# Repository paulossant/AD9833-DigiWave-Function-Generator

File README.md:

# AD9833-DigiWave-Function-Generator
DigiWave - Function Generator with STM32, analog amplification and touchscreen LCD

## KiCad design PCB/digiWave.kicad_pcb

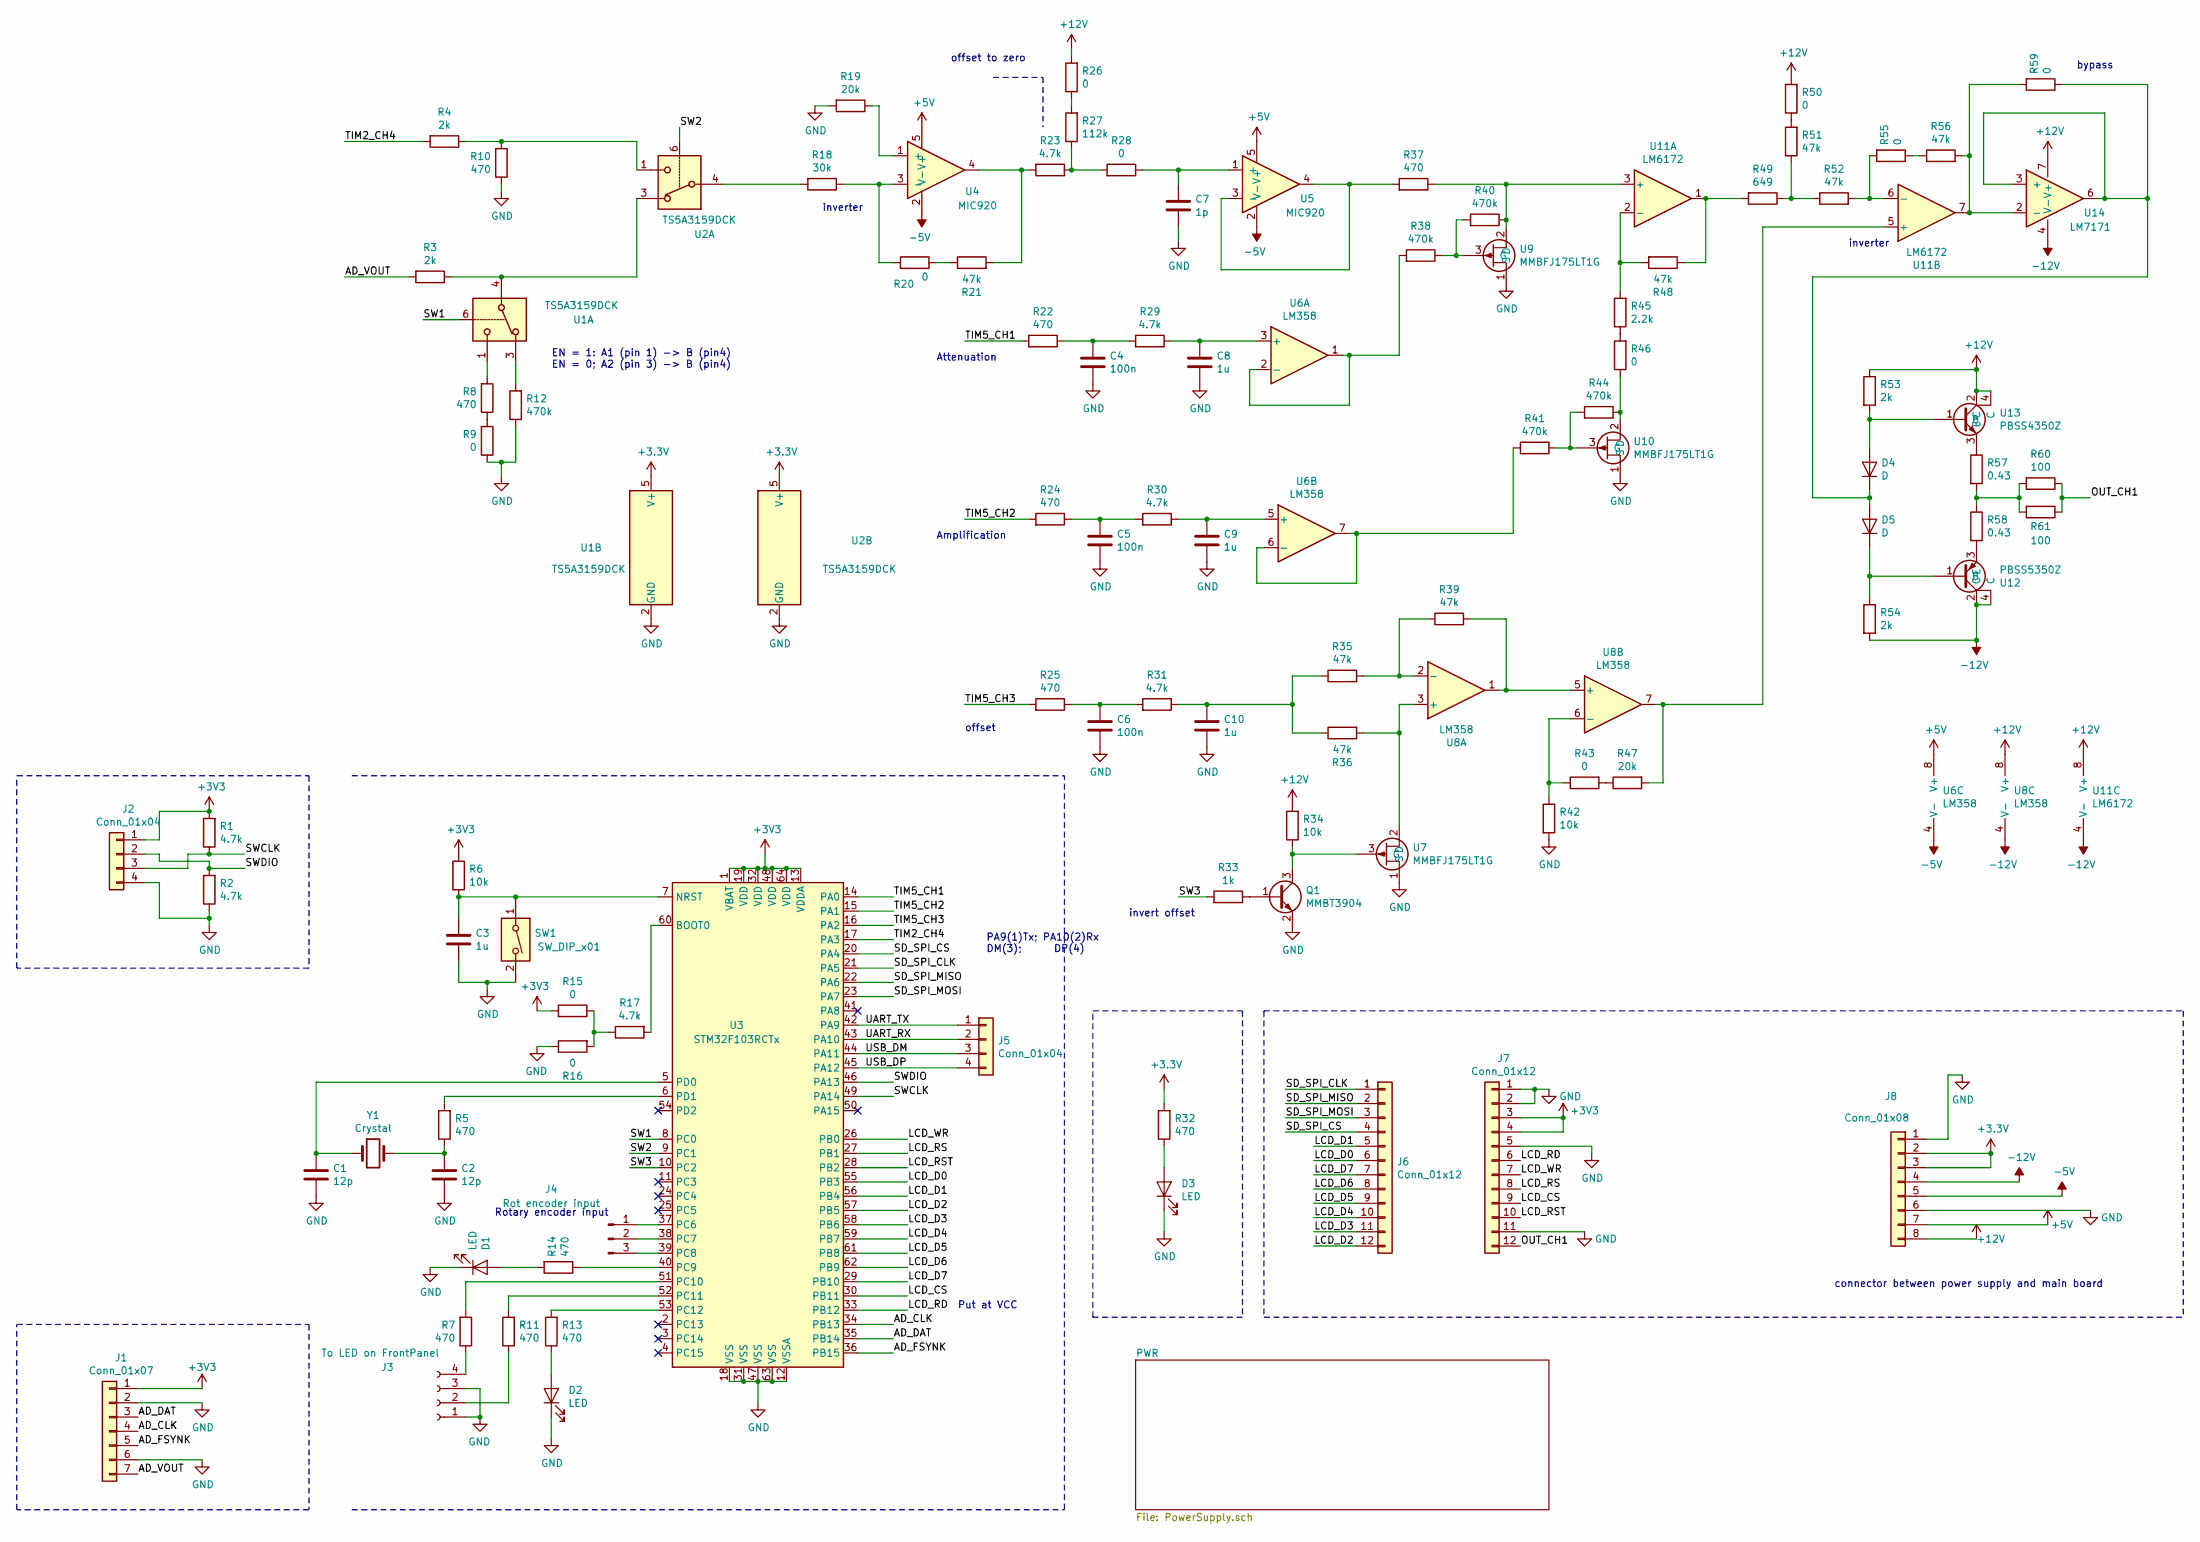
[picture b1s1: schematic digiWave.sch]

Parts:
C1, C2: 12p; C_0805_2012Metric_Pad1.15x1.40mm_HandSolder
C3, C8, C9, C10: 1u; C_0805_2012Metric_Pad1.15x1.40mm_HandSolder
C4, C5, C6: 100n; C_0805_2012Metric_Pad1.15x1.40mm_HandSolder
C7: 1p; C_0805_2012Metric_Pad1.15x1.40mm_HandSolder
D1, D2, D3: LED; LED_0805_2012Metric_Pad1.15x1.40mm_HandSolder
D4, D5: D; D_SOD-123
J1: Conn_01x07; PinHeader_1x07_P2.54mm_Vertical
J2, J5: Conn_01x04; PinHeader_1x04_P2.54mm_Vertical
J3: To LED on FrontPanel; PinSocket_1x04_P2.54mm_Vertical
J4: Rot encoder input; PinHeader_1x03_P2.54mm_Vertical
J6, J7: Conn_01x12; PinSocket_1x12_P2.54mm_Vertical
J8: Conn_01x08; PinHeader_1x08_P2.54mm_Vertical
Q1: MMBT3904; SOT-23_Handsoldering
R1, R2, R17, R23, R29, R30, R31: 4.7k; R_0805_2012Metric_Pad1.15x1.40mm_HandSolder
R3, R4, R53, R54: 2k; R_0805_2012Metric_Pad1.15x1.40mm_HandSolder
R5, R7, R8, R10, R11, R13, R14, R22, R24, R25, R32, R37: 470; R_0805_2012Metric_Pad1.15x1.40mm_HandSolder
R6, R34, R42: 10k; R_0805_2012Metric_Pad1.15x1.40mm_HandSolder
R9, R15, R16, R20, R26, R28, R43, R46, R50, R55, R59: 0; R_0805_2012Metric_Pad1.15x1.40mm_HandSolder
R12, R38, R40, R41, R44: 470k; R_0805_2012Metric_Pad1.15x1.40mm_HandSolder
R18: 30k; R_0805_2012Metric_Pad1.15x1.40mm_HandSolder
R19, R47: 20k; R_0805_2012Metric_Pad1.15x1.40mm_HandSolder
R21, R35, R36, R39, R48, R51, R52, R56: 47k; R_0805_2012Metric_Pad1.15x1.40mm_HandSolder
R27: 112k; R_0805_2012Metric_Pad1.15x1.40mm_HandSolder
R33: 1k; R_0805_2012Metric_Pad1.15x1.40mm_HandSolder
R45: 2.2k; R_0805_2012Metric_Pad1.15x1.40mm_HandSolder
R49: 649; R_0805_2012Metric_Pad1.15x1.40mm_HandSolder
R57, R58: 0.43; R_0805_2012Metric_Pad1.15x1.40mm_HandSolder
R60, R61: 100; R_1206_3216Metric_Pad1.42x1.75mm_HandSolder
SW1: SW_DIP_x01; SW_PUSH_6mm_H4.3mm
U1, U2: TS5A3159DCK; SOT-363_SC-70-6_Handsoldering
U3: STM32F103RCTx; QFP-64_10x10_Pitch0.5mm
U4, U5: MIC920; SOT-23-5_HandSoldering
U6, U8: LM358; SOIC-8_3.9x4.9mm_P1.27mm
U7, U9, U10: MMBFJ175LT1G; SOT-23_Handsoldering
U11: LM6172; SOIC-8_3.9x4.9mm_P1.27mm
U12: PBSS5350Z; SOT-223
U13: PBSS4350Z; SOT-223
U14: LM7171; SOIC-8_3.9x4.9mm_P1.27mm
Y1: Crystal; Crystal_HC49-4H_Vertical

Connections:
+5V: J8.7, U4.5 (V+), U5.5 (V+), U6.8 (V+)
+12V: J8.8, R26.2, R34.2, R50.2, R53.1, U8.8 (V+), U11.8 (V+), U13.2 (C), U13.4 (C), U14.7 (V+)
-5V: J8.5, U4.2 (V-), U5.2 (V-), U6.4 (V-)
-12V: J8.4, R54.2, U8.4 (V-), U11.4 (V-), U12.2 (C), U12.4 (C), U14.4 (V-)
/AD_CLK: J1.4, U3.34 (PB13)
/AD_DAT: J1.3, U3.35 (PB14)
/AD_FSYNK: J1.5, U3.36 (PB15)
/AD_VOUT: J1.7, R3.2
/LCD_CS: J7.9, U3.30 (PB11)
/LCD_D0: J6.6, U3.55 (PB3)
/LCD_D1: J6.5, U3.56 (PB4)
/LCD_D2: J6.12, U3.57 (PB5)
/LCD_D3: J6.11, U3.58 (PB6)
/LCD_D4: J6.10, U3.59 (PB7)
/LCD_D5: J6.9, U3.61 (PB8)
/LCD_D6: J6.8, U3.62 (PB9)
/LCD_D7: J6.7, U3.29 (PB10)
/LCD_RD: J7.6, U3.33 (PB12)
/LCD_RS: J7.8, U3.27 (PB1)
/LCD_RST: J7.10, U3.28 (PB2)
/LCD_WR: J7.7, U3.26 (PB0)
/OUT_CH1: J7.12, R60.1, R61.1
/SD_SPI_CLK: J6.1, U3.21 (PA5)
/SD_SPI_CS: J6.4, U3.20 (PA4)
/SD_SPI_MISO: J6.2, U3.22 (PA6)
/SD_SPI_MOSI: J6.3, U3.23 (PA7)
/SW1: U1.6, U3.8 (PC0)
/SW2: U2.6, U3.9 (PC1)
/SW3: R33.2, U3.10 (PC2)
/SWCLK: J2.3, R1.1, U3.49 (PA14)
/SWDIO: J2.2, R2.2, U3.46 (PA13)
/TIM2_CH4: R4.2, U3.17 (PA3)
/TIM5_CH1: R22.2, U3.14 (PA0)
/TIM5_CH2: R24.2, U3.15 (PA1)
/TIM5_CH3: R25.2, U3.16 (PA2)
/UART_RX: J5.2, U3.43 (PA10)
/UART_TX: J5.1, U3.42 (PA9)
/USB_DM: J5.3, U3.44 (PA11)
/USB_DP: J5.4, U3.45 (PA12)
GND: C1.2, C2.2, C3.1, C4.2, C5.2, C6.2, C7.2, C8.2, C9.2, C10.2, D1.1 (K), D2.1 (K), D3.1 (K), J1.2, J1.6, J2.4, J3.1, J3.3, J7.1, J7.2, J7.5, J7.11, J8.1, J8.6, Q1.2 (E), R2.1, R9.1, R10.1, R12.1, R16.1, R19.2, R42.2, SW1.2, U1.2 (GND), U2.2 (GND), U3.12 (VSSA), U3.18 (VSS), U3.31 (VSS), U3.47 (VSS), U3.63 (VSS), U7.1 (S), U9.1 (S), U10.1 (S); also elsewhere on the board
unnamed: C1.1, U3.5 (PD0), Y1.1
unnamed: C2.1, R5.1, Y1.2
unnamed 50: C3.2, R6.2, SW1.1, U3.7 (NRST); also elsewhere on the board
unnamed: C4.1, R22.1, R29.2
unnamed: C5.1, R24.1, R30.2
unnamed: C6.1, R25.1, R31.2
unnamed: C7.1, R28.1, U5.1 (+)
unnamed: C8.1, R29.1, U6.3 (+)
unnamed: C9.1, R30.1, U6.5 (+)
unnamed: C10.1, R31.1, R35.1, R36.1
unnamed: D1.2 (A), R14.2
unnamed: D2.2 (A), R13.1
unnamed: D3.2 (A), R32.1
unnamed: D4.1 (K), D5.2 (A), R59.1, U14.3 (+), U14.6
unnamed: D4.2 (A), R53.2, U13.1 (B)
unnamed: D5.1 (K), R54.1, U12.1 (B)
unnamed: J3.2, R11.1
unnamed: J3.4, R7.1
unnamed: J4.1, U3.37 (PC6)
unnamed: J4.2, U3.38 (PC7)
unnamed: J4.3, U3.39 (PC8)
unnamed: Q1.1 (B), R33.1
unnamed: Q1.3 (C), R34.1, U7.3 (G)
unnamed: R3.1, U1.4, U2.3
unnamed: R5.2, U3.6 (PD1)
unnamed: R7.2, U3.51 (PC10)
unnamed: R8.1, R9.2
unnamed: R8.2, U1.1
unnamed: R4.1, R10.2, U2.1
unnamed: R11.2, U3.52 (PC11)
unnamed: R12.2, U1.3
unnamed: R13.2, U3.53 (PC12)
unnamed: R14.1, U3.40 (PC9)
unnamed: R15.1, R16.2, R17.1
unnamed: R17.2, U3.60 (BOOT0)
unnamed: R18.1, R20.2, U4.3 (-)
unnamed: R18.2, U2.4
unnamed: R19.1, U4.1 (+)
unnamed: R20.1, R21.1
unnamed: R21.2, R23.2, U4.4
unnamed: R23.1, R27.1, R28.2
unnamed: R26.1, R27.2
unnamed: R35.2, R39.1, U8.2 (-)
unnamed: R36.2, U7.2 (D), U8.3 (+)
unnamed: R37.1, R40.1, U9.2 (D), U11.3 (+)
unnamed: R37.2, U5.3 (-), U5.4
unnamed: R38.1, R40.2, U9.3 (G)
unnamed: R38.2, U6.1, U6.2 (-)
unnamed: R39.2, U8.1, U8.5 (+)
unnamed: R41.1, R44.2, U10.3 (G)
unnamed: R41.2, U6.6 (-), U6.7
unnamed: R42.1, R43.1, U8.6 (-)
unnamed: R43.2, R47.1
unnamed: R44.1, R46.1, U10.2 (D)
unnamed: R45.1, R46.2
unnamed: R45.2, R48.2, U11.2 (-)
unnamed: R47.2, U8.7, U11.5 (+)
unnamed: R48.1, R49.2, U11.1
unnamed: R49.1, R51.1, R52.1
unnamed: R50.1, R51.2
unnamed: R52.2, R55.2, U11.6 (-)
unnamed: R55.1, R56.1
unnamed: R56.2, R59.2, U11.7, U14.2 (-)
unnamed: R57.1, U13.3 (E)
unnamed: R57.2, R58.1, R60.2, R61.2
unnamed: R58.2, U12.3 (E)

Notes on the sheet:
Put at VCC
offset to zero
bypass
EN = 1: A1 (pin 1) -> B (pin4) EN = 0; A2 (pin 3) -> B (pin4)
Attenuation
Amplification
invert offset
offset
inverter
connector between power supply and main board
PA9(1)Tx; PA10(2)Rx DM(3); DP(4)
Rotary encoder input

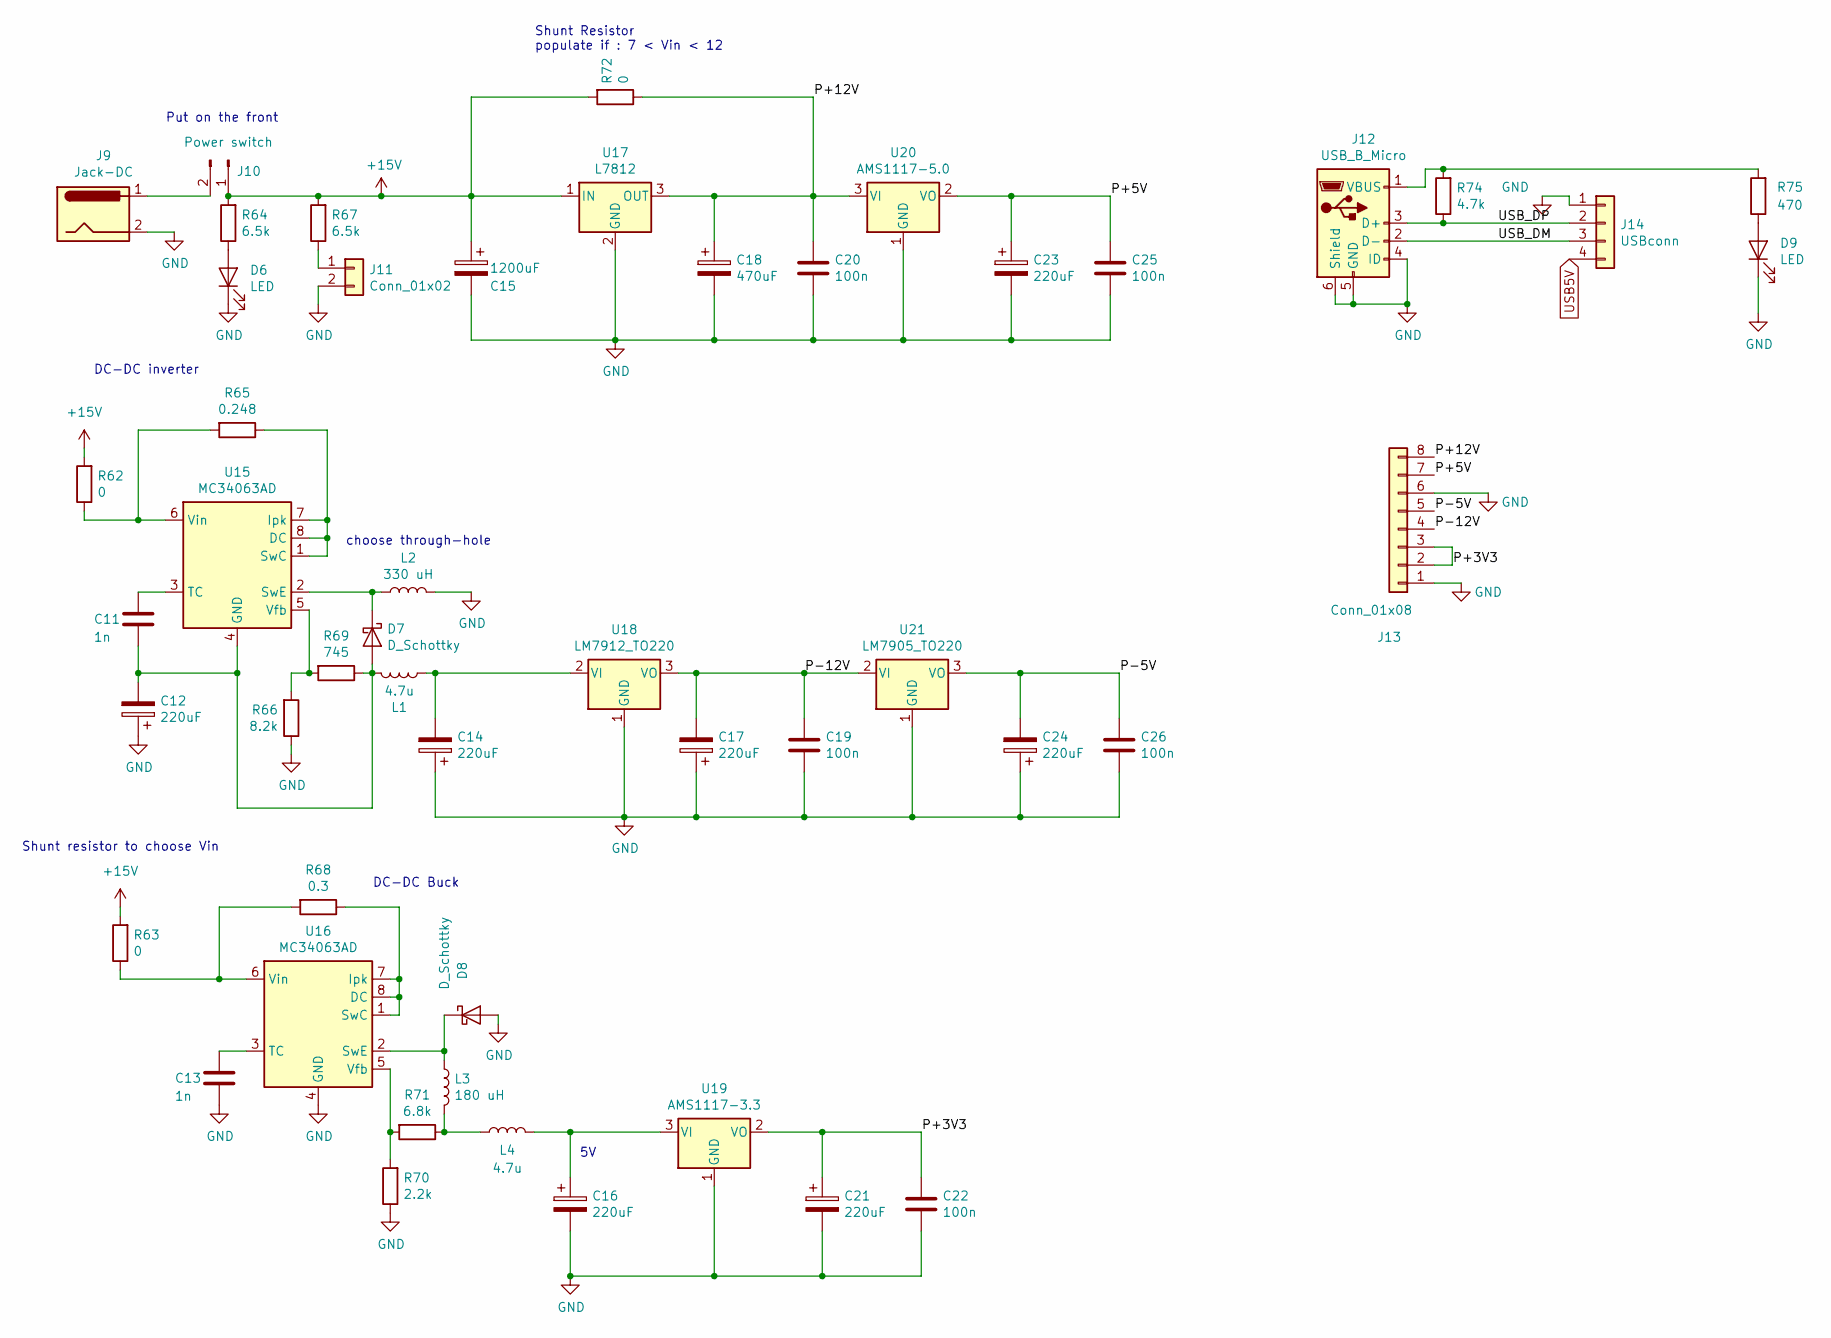
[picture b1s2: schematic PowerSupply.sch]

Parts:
C11, C13: 1n; C_Disc_D3.8mm_W2.6mm_P2.50mm
C12, C14, C16, C17, C21, C23, C24: 220uF; CP_Radial_D6.3mm_P2.50mm
C15: 1200uF; CP_Radial_D12.5mm_P5.00mm
C18: 470uF; CP_Radial_D8.0mm_P3.50mm
C19, C20, C22, C25, C26: 100n; C_0805_2012Metric_Pad1.15x1.40mm_HandSolder
D6, D9: LED; LED_0805_2012Metric_Pad1.15x1.40mm_HandSolder
D7, D8: D_Schottky; D_1812_4532Metric_Pad1.30x3.40mm_HSolder
J9: Jack-DC; Connector_BarrelJack
J10: Power switch; PinHeader_1x02_P2.54mm_Vertical
J11: Conn_01x02; PinHeader_1x02_P2.54mm_Vertical
J12: USB_B_Micro; USB_Micro-B_mine
J13: Conn_01x08; PinHeader_1x08_P2.54mm_Vertical
J14: USBconn; PinHeader_1x04_P2.54mm_Vertical
L1, L4: 4.7u; L_0805_2012Metric_Pad1.15x1.40mm_HandSolder
L2: 330 uH; L_Radial_D9.5mm_P5.00mm_Fastron_07HVP
L3: 180 uH; L_Radial_D9.5mm_P5.00mm_Fastron_07HVP
R62, R63, R72: 0; R_0805_2012Metric_Pad1.15x1.40mm_HandSolder
R64, R67: 6.5k; R_0805_2012Metric_Pad1.15x1.40mm_HandSolder
R65: 0.248; R_0805_2012Metric_Pad1.15x1.40mm_HandSolder
R66: 8.2k; R_0805_2012Metric_Pad1.15x1.40mm_HandSolder
R68: 0.3; R_0805_2012Metric_Pad1.15x1.40mm_HandSolder
R69: 745; R_0805_2012Metric_Pad1.15x1.40mm_HandSolder
R70: 2.2k; R_0805_2012Metric_Pad1.15x1.40mm_HandSolder
R71: 6.8k; R_0805_2012Metric_Pad1.15x1.40mm_HandSolder
R74: 4.7k; R_0805_2012Metric_Pad1.15x1.40mm_HandSolder
R75: 470; R_0805_2012Metric_Pad1.15x1.40mm_HandSolder
U15, U16: MC34063AD; SOIC-8_3.9x4.9mm_P1.27mm
U17: L7812; TO-220-3_Vertical
U18: LM7912_TO220; TO-220-3_Vertical
U19: AMS1117-3.3; SOT-223-3_TabPin2
U20: AMS1117-5.0; SOT-223-3_TabPin2
U21: LM7905_TO220; TO-220-3_Vertical

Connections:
+15V: C15.1, J10.1, R62.2, R63.2, R64.2, R67.2, R72.2, U17.1 (IN)
/PWR/P+3V3: C21.1, C22.1, J13.2, J13.3, U19.2 (VO)
/PWR/P+5V: C23.1, C25.1, J13.7, U20.2 (VO)
/PWR/P+12V: C18.1, C20.1, J13.8, R72.1, U17.3 (OUT), U20.3 (VI)
/PWR/P-5V: C24.2, C26.1, J13.5, U21.3 (VO)
/PWR/P-12V: C17.2, C19.1, J13.4, U18.3 (VO), U21.2 (VI)
/PWR/USB_DM: J12.2 (D-), J14.3
/PWR/USB_DP: J12.3 (D+), J14.2, R74.1
GND: C12.1, C13.2, C14.1, C15.2, C16.2, C17.1, C18.2, C19.2, C20.2, C21.2, C22.2, C23.2, C24.1, C25.2, C26.2, D6.1 (K), D8.2 (A), D9.1 (K), J9.2, J11.2, J12.4 (ID), J12.5 (GND), J12.6 (Shield), J13.1, J13.6, J14.1, L2.2, R66.1, R70.1, U16.4 (GND), U17.2 (GND), U18.1 (GND), U19.1 (GND), U20.1 (GND), U21.1 (GND); also elsewhere on the board
unnamed: C11.1, U15.3 (TC)
unnamed: C11.2, C12.2, D7.2 (A), L1.2, R69.1, U15.4 (GND)
unnamed: C13.1, U16.3 (TC)
unnamed: C14.2, L1.1, U18.2 (VI)
unnamed: C16.1, L4.2, U19.3 (VI)
unnamed: D6.2 (A), R64.1
unnamed: D7.1 (K), L2.1, U15.2 (SwE)
unnamed: D8.1 (K), L3.1, U16.2 (SwE)
unnamed: D9.2 (A), R75.1
unnamed: J9.1, J10.2
unnamed: J11.1, R67.1
unnamed: J12.1 (VBUS), R74.2, R75.2
unnamed: L3.2, L4.1, R71.1
unnamed: R62.1, R65.2, U15.6 (Vin)
unnamed: R63.1, R68.2, U16.6 (Vin)
unnamed: R65.1, U15.1 (SwC), U15.7 (Ipk), U15.8 (DC)
unnamed: R66.2, R69.2, U15.5 (Vfb)
unnamed: R68.1, U16.1 (SwC), U16.7 (Ipk), U16.8 (DC)
unnamed: R70.2, R71.2, U16.5 (Vfb)

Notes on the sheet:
DC-DC Buck
DC-DC inverter
choose through-hole
Put on the front
Shunt Resistor populate if : 7 < Vin < 12
Shunt resistor to choose Vin

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
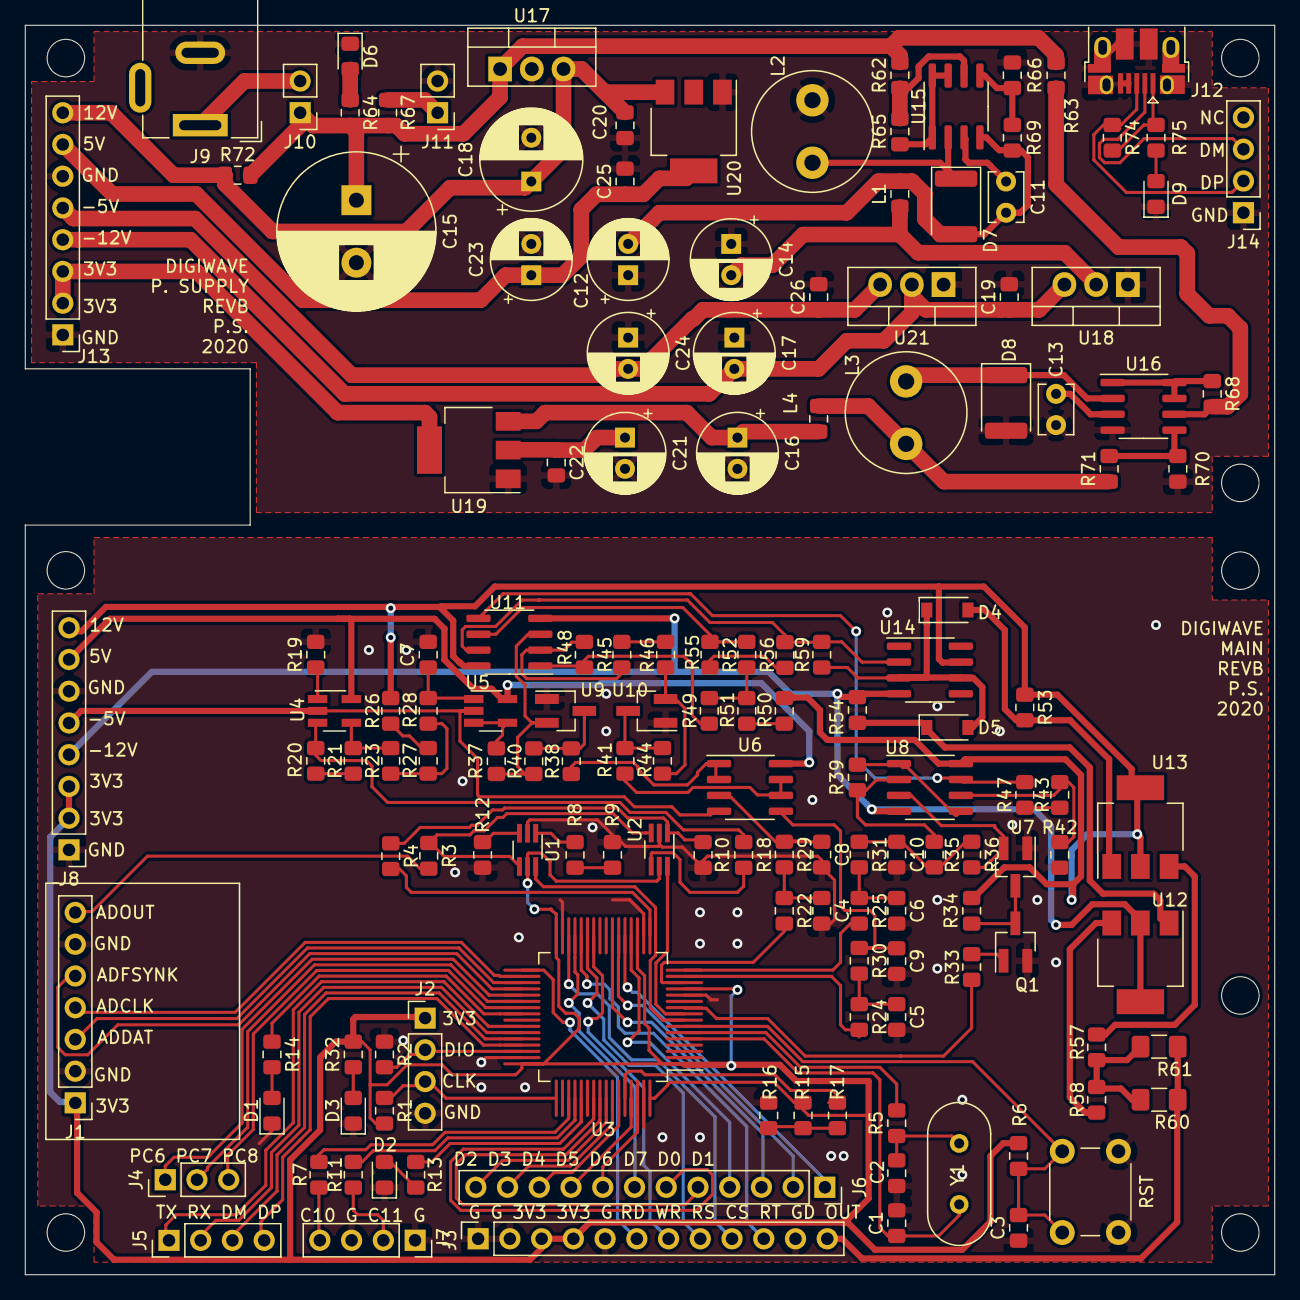
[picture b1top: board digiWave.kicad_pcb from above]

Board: 2 copper layers, 100.0 x 100.0 mm, 151 parts (0 on the bottom side), 134 nets.

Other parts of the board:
RST: SW_DIP_x01; SW_PUSH_6mm_H4.3mm

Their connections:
GND: RST.2; also elsewhere on the board
unnamed 50: RST.1; also elsewhere on the board
